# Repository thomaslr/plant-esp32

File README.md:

# 🌿 Plant Monitor & Automated Irrigation Controller (ESP32-C3 Rust)

An industrial-grade, memory-safe automated plant watering and environmental monitoring system built for the ultra-compact **ESP32-C3 SuperMini** (32-bit RISC-V) running on **ESP-IDF** and written in **bare-metal Rust**.

Features:
- **Zero Heap Fragmentation & Crash-Resilience:** Complete domain logic written in memory-safe Rust with 66+ unit tests passing on host (`cargo test`).
- **Dual-Slot A/B Over-The-Air (OTA) Updates:** Dual 1984 KB partitions (`ota_0` / `ota_1`) with hardware bootloader rollback (`CONFIG_BOOTLOADER_APP_ROLLBACK_ENABLE`). If a newly flashed firmware encounters an error, the chip automatically reverts to the previous working slot.
- **Embedded Web Dashboard & PWA:** Self-hosted interactive web dashboard embedded directly in flash via `include_str!`, installable as an offline-capable PWA on iOS, Android, and Desktop.
- **Fail-Safe Plant Protection:** Multi-tiered safety supervisor enforcing daily watering limits, minimum cycle cooldowns, dry tank cutoffs, and night-time quiet hours.
- **Self-Healing Wi-Fi Provisioning:** Captive portal (`PlantMonitor-Setup-XXXX`) with a 5-minute watchdog recovery timer that auto-reconnects when home routers recover after outages.
- **Deterministic Multi-Fault LED Supervisor:** Non-blocking blue LED telemetry signaling Wi-Fi status, pump state, active faults, and flash writing strobes.

---

## 🚀 Quick Start & Installation

Ready to get started? Check out our dedicated step-by-step guide:

👉 **[Complete Quick Start & Flashing Guide (QUICKSTART.md)](QUICKSTART.md)**

### At a Glance: Zero-Install Pre-Built Binaries

Every GitHub release includes two binary formats on the **[Releases Page](https://github.com/thomaslr/plant-esp32/releases)**:

| Binary File | Flash Address | Purpose & Usage |
| :--- | :---: | :--- |
| **`plant-firmware-factory.bin`** | **`0x0`** | **Initial Setup / First-Time Flashing:** Merged factory binary with ESP32-C3 bootloader, Dual-OTA partition table (`ota_0` and `ota_1`), and application code. Flashes blank chips in one shot via Chrome/Edge Web Flasher or USB CLI. |
| **`plant-firmware.bin`** | OTA Partition | **Wi-Fi Updates (OTA):** Standalone application payload uploaded via the web interface (`http://plants1.local`) or downloaded automatically during remote updates. |

* **1-Click Browser Flashing:** Open [Espressif Web Flasher](https://espressif.github.io/esptool-js/) in Chrome/Edge, connect your ESP32-C3 SuperMini at `460800` baud, and flash `plant-firmware-factory.bin` at `0x0`.
* **Single-Command CLI:** `esptool.py --chip esp32c3 write_flash 0x0 plant-firmware-factory.bin`
* **First-Time Wi-Fi Setup:** Connect to the `PlantMonitor-Setup-XXXX` hotspot at `http://192.168.4.1` to configure your Wi-Fi credentials.

See **[QUICKSTART.md](QUICKSTART.md)** for complete hardware checklists, bootloader button timings, and troubleshooting.

---

## 📌 Hardware Pinout Reference (ESP32-C3 SuperMini)

Canonical Pinout Reference: [LastMinuteEngineers ESP32-C3 SuperMini Pinout](https://lastminuteengineers.com/esp32-c3-super-mini-pinout-reference/)

| ESP32-C3 Pin | Connected Component | Function & Conditioning | Mode |
| :--- | :--- | :--- | :--- |
| **GPIO 0** | 18650 Battery Monitor | ADC1_CH0 via 100kΩ/100kΩ divider (R8/R9) + 100nF (C6) | Analog IN |
| **GPIO 1** | Ambient Light Sensor | ADC1_CH1 via LDR1 + 10kΩ divider (R7) + 100nF (C4) | Analog IN |
| **GPIO 2** | Strapping Protected | **Unconnected / High-Z** (Zero boot hangs) | High-Z |
| **GPIO 3** | Capacitive Soil Sensor | ADC1_CH3 connected to TB2 Pin 1 (`AOUT`) + 100nF filter (C2) | Analog IN |
| **GPIO 4** | 5V Supply Rail Monitor | ADC1_CH4 via 100kΩ/100kΩ divider (R1/R2) + 100nF filter (C1) | Analog IN |
| **GPIO 5** | I2C SCL | I2C Clock bus for optional SHT30 / BH1750 modules | Open Drain |
| **GPIO 6** | I2C SDA | I2C Data bus for optional SHT30 / BH1750 modules | Open Drain |
| **GPIO 7** | Ultrasonic Sensor `TRIG`| 10 µs trigger pulse output to HC-SR04 (TB1 Pin 2) | Digital OUT |
| **GPIO 8** | Onboard Status LED | Active LOW blue LED (Active: 0, Inactive: 1) | Digital OUT |
| **GPIO 9** | BOOT Button | Onboard tactile button (pulls LOW when pressed) | Digital IN |
| **GPIO 10** | Pump MOSFET Gate | Digital output to AO3400A Gate via 1kΩ (R5) + 100kΩ pull-down (R6) | Digital OUT |
| **GPIO 20** | Ultrasonic Sensor `ECHO`| Digital input via 1kΩ/2kΩ divider (R3/R4) stepping 5V down to 3.3V | Digital IN |
| **GPIO 21** | Switched Soil Sensor VCC | Digital switched 3.3V power to TB2 Pin 2 (Duty-cycled reading) | Digital OUT |

---

## 🛡️ Multi-Tiered Safety Supervisor

The watering pump can **never** physically run unless all safety invariants are satisfied simultaneously:
1. **Hardware Watchdog Timer (WDT):** 5-second hardware timeout resets the CPU if the scheduler stalls, pulling GPIO 10 LOW via R6 (100kΩ).
2. **Maximum Continuous Pump Runtime:** Hard cutoff after 60 seconds prevents tank emptying during pipe fractures.
3. **Minimum Cycle Cooldown:** Mandatory 300-second pause between watering events allows water absorption into soil substrate.
4. **Daily Cumulative Watering Limit:** Prevents root drowning by capping total daily watering duration (e.g. 93 seconds/day max), resetting at local midnight via SNTP.
5. **Night-Watering Protection:** Automated watering is inhibited during night quiet hours (default: 10:00 PM to 9:00 AM).
6. **Dry Tank Interlock:** Blocks automated and manual pump activation when reservoir water level is below 2.0 cm.

---

## 🔄 Dual-Slot Over-The-Air (OTA) Updates

The ESP32-C3 uses a custom 4MB partition table (`plant-firmware/partitions.csv`):
```text
nvs,      data, nvs,     0x9000,   0x6000,   # 24 KB User config & Wi-Fi credentials
otadata,  data, ota,     0xf000,   0x2000,   # 8 KB Active boot slot pointers (A/B state)
phy_init, data, phy,     0x11000,  0x1000,   # 4 KB RF calibration data
ota_0,    app,  ota_0,   0x20000,  0x1f0000, # 1984 KB Application Slot 0 (Active / Standby)
ota_1,    app,  ota_1,   0x210000, 0x1f0000, # 1984 KB Application Slot 1 (Active / Standby)
```

- When an update is initiated from the Web Dashboard or REST API, the firmware streams `plant-firmware.bin` from GitHub Releases into the inactive slot (`ota_0` or `ota_1`).
- On reboot, the bootloader attempts to boot the new slot. If it crashes or fails to call `mark_running_slot_valid()`, the bootloader automatically rolls back to the previous known-good firmware slot.

---

## 💡 Status LED Signal Reference

The onboard blue LED (GPIO 8) on the ESP32-C3 SuperMini provides real-time visual feedback:

| LED Pattern | Meaning & State |
| :--- | :--- |
| **💙 Single 100ms Pulse (every 10s)** | **Normal Healthy Idle:** All sensors within bounds, Wi-Fi connected. |
| **🌊 Solid ON** | **Watering Active:** Pump motor is running. |
| **⚡ 10 Hz Strobe (Continuous)** | **OTA Flashing:** Flash memory write in progress — do not unplug. |
| **📶 200ms ON / 800ms OFF** | **Wi-Fi Connecting / SoftAP:** In setup portal or negotiating router. |
| **🌐 Rapid Double Blip** | **Web Traffic:** Incoming HTTP REST API or dashboard request. |
| **⚠️ 3 Pulses + Pause** | **Soil Moisture Sensor Fault:** Disconnected or voltage out of bounds. |
| **⚠️ 4 Pulses + Pause** | **Ultrasonic Sensor Fault:** Echo timeout, echo blocked, or disconnected. |
| **📉 Accelerando Frequency Sweep** | **Reservoir Empty:** Water level below dry run safety threshold. |
| **🔘 Solid ON (held) + 5 Rapid Blips** | **Hardware Factory Reset:** Hold `BOOT` button (GPIO 9) for 5s until LED blinks 5 times to confirm wipe. |

---

## 🏠 Home Assistant Integration

Integrate the plant monitor into Home Assistant using standard REST sensors:

```yaml
# configuration.yaml
sensor:
  - platform: rest
    name: "Plant Monitor"
    resource: "http://plants1.local/api/telemetry"
    scan_interval: 30
    json_attributes:
      - soil_moisture_pct
      - water_level_pct
      - water_level_cm
      - light_level_pct
      - dli
      - battery_voltage_mv
      - is_watering
      - wifi_rssi
    value_template: "{{ 'online' if value_json.is_watering is defined else 'offline' }}"

  - platform: template
    sensors:
      plant_soil_moisture:
        friendly_name: "Soil Moisture"
        unit_of_measurement: "%"
        value_template: "{{ state_attr('sensor.plant_monitor', 'soil_moisture_pct') | round(1) }}"
        icon_template: mdi:flower
      plant_water_level:
        friendly_name: "Water Level"
        unit_of_measurement: "%"
        value_template: "{{ state_attr('sensor.plant_monitor', 'water_level_pct') | round(1) }}"
        icon_template: mdi:water-percent
      plant_light_dli:
        friendly_name: "Daily Light Integral (DLI)"
        unit_of_measurement: "mol/m²/d"
        value_template: "{{ state_attr('sensor.plant_monitor', 'dli') | round(2) }}"
        icon_template: mdi:white-balance-sunny

# Manual Watering Trigger Action
rest_command:
  water_plant:
    url: "http://plants1.local/api/water"
    method: POST
    content_type: "application/json"
    payload: '{"duration_sec": 5}'
```

---

## 📂 Repository Structure

```
plant-esp32/
├── .github/workflows/          # CI/CD: Automated builds and release publishing
│   └── build-and-release.yml   # Multi-binary builder (factory + OTA .bin)
├── data/                       # Embedded Web Frontend (HTML, CSS, JS, PWA manifest)
├── installer/                  # ESP Web Tools 1-click in-browser web installer
├── firmware-rust/              # Rust Cargo Workspace
│   ├── Cargo.toml
│   ├── plant-core/             # Platform-independent domain logic, safety supervisor, math
│   └── plant-firmware/         # ESP-IDF firmware application, HAL, HTTP server, OTA client
├── pcb/                        # KiCad PCB project, schematics, and manufacturing Gerbers
├── enclosure/                  # 3D printable CAD models and enclosures
├── scripts/                    # Developer helper scripts (flashing, pin tests)
├── QUICKSTART.md               # First-time setup, flashing & provisioning guide
├── PROJECT.md                  # Comprehensive architectural system specification
└── CHANGELOG.md                # Firmware changelog history
```

---

## 📄 License

This project is open source and dual-licensed across software and hardware (see [LICENSE](LICENSE) for full details):

| Component | Directories | License |
| :--- | :--- | :--- |
| **Software & Web UI** | [`firmware-rust/`](firmware-rust/), [`data/`](data/), [`installer/`](installer/), [`scripts/`](scripts/) | **[GNU GPLv3](LICENSE-SOFTWARE)** (`GPL-3.0-only`) |
| **Hardware & Enclosure** | [`pcb/`](pcb/), [`enclosure/`](enclosure/) | **[CERN-OHL-S v2](LICENSE-HARDWARE)** (`CERN-OHL-S-2.0`) |

### Commercial Licensing Available

Tinkerers, makers, and researchers are free to build, modify, and share this project under **GPLv3** and **CERN-OHL-S v2** (preserving attribution and publishing any distributed modifications under the same license).

Companies or organizations wishing to use, modify, or manufacture this project in a **closed-source or proprietary commercial product** without reciprocal source-disclosure obligations—or seeking official brand/trademark licensing—can obtain a commercial license. See [LICENSE](LICENSE) for contact details.

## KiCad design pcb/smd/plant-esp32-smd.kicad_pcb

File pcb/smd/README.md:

# Plant ESP32 Controller — Turnkey SMD / PCBA Edition (Rev 2.3)

This directory contains the production files, Pick & Place centroid files, Bill of Materials, and KiCad designs for the **Turnkey Surface Mount (SMD) Edition** of the Plant ESP32 watering controller.

Optimized specifically for **JLCPCB SMT Assembly** using **100% Basic Parts Library components** for zero feeder change fees ($0 setup fees).

---

## 3D Previews & Interactive Diagram

| Top View (SMD Components & Silkscreen) | Isometric 3D View (SMD) |
| :---: | :---: |
|  |  |

| Bottom View (Solid Ground Plane Pour & Power Routing) |
| :---: |
|  |

👉 **Interactive SVG Circuit Diagram & Net Visualizer:** [`circuit_diagram_smd.html`](circuit_diagram_smd.html)

---

## Architectural Highlights (Rev 2.3)

* **100% Top-Side SMT Placement**: All SMD parts are on the `F.Cu` / `F.Paste` layer, requiring only single-sided stencil setup ($0 double-sided setup fees).
* **100% Basic Parts Library ($0 Feeder Fees)**: All 8 unique SMD parts (R1–R9, C1–C6, D1, D2, Q1) are selected from JLCPCB's permanent Basic Parts catalog. Total feeder setup fee: **\$0.00**.
* **Authoritative Pinout Reference**: All pins match the official [LastMinuteEngineers ESP32-C3 SuperMini Pinout Reference](https://lastminuteengineers.com/esp32-c3-super-mini-pinout-reference/).
* **Dedicated Dual ADC Voltage Monitoring (Zero Jumpers!)**:
  * **No selector header or jumper shunt required (`JP1` eliminated completely)**. Both voltages are sampled concurrently in real time by firmware!
  * **5V Supply Rail Monitor (GPIO 4 / `ADC1_CH4`)**: Dedicated 100 kΩ / 100 kΩ divider (`R1`, `R2`, `#C149504`) + 100 nF filter (`C1`, `#C28233`). Monitors USB/Mains 5V health and detects pump brownouts.
  * **18650 Battery Monitor (GPIO 0 / `ADC1_CH0`)**: Dedicated 100 kΩ / 100 kΩ divider (`R8`, `R9`, `#C149504`) + 100 nF filter (`C6`, `#C28233`). Directly measures raw 18650 Li-ion battery voltage ($3.0\text{V}\text{–}4.2\text{V}$) from `TB4 Pin 3 (BAT)`. Quiescent drain is **only 21 µA** ($\sim 15\text{ mAh}$ per month), far below the battery's chemical self-discharge!
  * Both channels reside on **ADC1**, guaranteeing 100% reliable concurrent analog reads during active Wi-Fi streaming.
* **External Solar / 18650 Battery Power Terminal (`TB4`, DNP)**:
  * 3-pin KF301 screw terminal block (5.00 mm pitch) located on the right edge with wire entries facing outwards (`+X`).
  * **Pin 1 (`EXT_5V`)**: Regulated 5.0V power input from a solar charge & boost module (e.g. DD05CVSA mini-UPS).
  * **Pin 2 (`GND`)**: Common system ground.
  * **Pin 3 (`BAT`)**: Direct connection to the 18650 Li-ion battery positive terminal (`BAT+`) for true state-of-charge monitoring.
* **Anti-Backfeeding Schottky Diode Protection (`D2`)**:
  * **SS34** (SMA / DO-214AC package, 40V 3A Schottky rectifier, JLCPCB Basic Part `#C8678`, \$0 fee).
  * Placed in series between `TB4-1` (`EXT_5V`) and the internal `+5V` power rail.
  * When USB-C is plugged into the ESP32 while the battery/solar module is connected, `D2` is reverse-biased and **physically blocks 100% of reverse current** from backfeeding into the booster or solar charger.
  * Ultra-low forward drop ($\sim 0.25\text{–}0.35\text{V}$) delivers $\sim 4.75\text{V}$ to the board under pump load, well above the 3.5V ESP32 LDO brownout limit.
* **Flyback Diode (`D1`)**: **SS34** (SMA / DO-214AC package, 40V 3A Schottky rectifier, JLCPCB Basic Part `#C8678`, shared reel with D2).
* **Logic-Level High-Current MOSFET (`Q1`)**: **AO3400A** (SOT-23-3, 30V 5.7A, $V_{GS(th)} \approx 0.65\text{–}1.45\text{V}$, $R_{DS(on)} < 0.033\,\Omega$, LCSC `#C20917`). Gate driven by **GPIO 10**.
* **Dual-Stage Brownout & High-Frequency Decoupling**:
  * **Factory Pre-Soldered Ceramics (`C3`, `C5`)**: 2× 10 µF 25V 0805 MLCCs (LCSC `#C15850`, Basic Part, $0 fee). Total 20 µF with ultra-low ESR ($< 0.02\,\Omega$) handles microsecond motor startup dips and Wi-Fi bursts.
  * **Through-Hole Brownout Expansion (`C_EXT`, DNP)**: 2.50 mm pitch radial footprint (labeled `OPT BULK` on silkscreen, supporting Ø6.3 mm to Ø10.0 mm cans) located on the far right directly adjacent to pump terminal TB3 (>55 mm away from the ESP32 USB-C port). Leaves the entire USB-C corridor 100% unobstructed.
* **Switched Soil Sensor Power on GPIO 21 & Analog DATA on GPIO 3**:
  * Duty-cycled soil power is assigned to `GPIO 21` (digital out on header J2-8, routed to `TB2-2`).
  * Capacitive probe analog output is sampled on `GPIO 3` (`ADC1_CH3` on header J1-5, routed from `TB2-1`).
* **Ambient Light Sensor LDR Divider on GPIO 1 (`ADC1_CH1`)**:
  * **Zero Boot Strapping Risk**: Placed on **GPIO 1** (`ADC1_CH1`) to completely eliminate boot hangs.
  * **LDR1 (DNP)**: 2-pin through-hole footprint (2.54 mm pitch) for **GL5506, GL5516, GL5528, GL5537, GL5539** photoresistors.
  * **R7 (10 kΩ 0805 SMD)**: Factory pre-soldered basic part ($V_{out} \to$ GPIO 1).
  * **C4 (100 nF 0805 SMD)**: Factory pre-soldered basic part for AC light flicker suppression.
  * **100% Wi-Fi Safe**: Because GPIO 1 is on **ADC1**, `analogRead(1)` functions seamlessly while Wi-Fi is actively streaming.
* **Ultrasonic Sensor on GPIO 7 (TRIG) & GPIO 20 (ECHO)**:
  * Ultrasonic TRIG is assigned to **GPIO 7** (digital out on header J2-3, routed to `TB1-2`).
  * Ultrasonic ECHO is assigned to **GPIO 20** via the 1k/2k 0805 level divider (`TB1-3` $\to$ R3/R4 $\to$ J2-7).
* **GPIO 2 Left Unconnected**: Protected strapping pin left free on header J1-6 to ensure rock-solid boot reliability under all conditions.
* **I2C Expansion Ports for SHT30 & BH1750 (DNP)**:
  * **MOD1 (SHT30 Socket)**: 4-pin header (`3V3`, `GND`, `SCL` $\to$ GPIO 5, `SDA` $\to$ GPIO 6).
  * **MOD2 (BH1750 Socket)**: 5-pin header (`VCC`, `GND`, `SCL` $\to$ GPIO 5, `SDA` $\to$ GPIO 6, `ADD` $\to$ GND for default `0x23` address).
  * Both headers are left unpopulated (DNP) by JLCPCB at **\$0.00 extra cost**, giving an instant drop-in upgrade path.

---

## Bill of Materials (BOM) & LCSC Part Mapping

| Designator | Value / Description | Package | JLCPCB Part # (LCSC) | Type | Role |
| :--- | :--- | :--- | :--- | :--- | :--- |
| **R1, R2, R6, R8, R9** | 100 kΩ (1%, 1/8W) | 0805 SMD | **C149504** | Basic (\$0 Fee) | 5V Divider / Battery Divider (21µA drain) / Gate Pull-Down |
| **R7** | 10 kΩ (1%, 1/8W) | 0805 SMD | **C17414** | Basic (\$0 Fee) | LDR Ambient Light Sensor Divider |
| **R3, R5** | 1 kΩ (1%, 1/8W) | 0805 SMD | **C17513** | Basic (\$0 Fee) | Echo Divider High-Side / Gate Current Limiter |
| **R4** | 2 kΩ (1%, 1/8W) | 0805 SMD | **C17604** | Basic (\$0 Fee) | Echo Divider Low-Side ($5\text{V} \to 3.3\text{V}$) |
| **C1, C2, C4, C6** | 100 nF (50V X7R) | 0805 SMD | **C28233** | Basic (\$0 Fee) | 5V ADC Filter / Soil RF Bypass / Light Filter / Battery ADC Filter |
| **C3, C5** | 10 µF (25V X5R) | 0805 SMD | **C15850** | Basic (\$0 Fee) | 5V Power Rail Transient Decoupling (20 µF Total) |
| **D1, D2** | SS34 (3A, 40V Schottky Barrier Diode) | SMA (DO-214AC) | **C8678** | Basic (\$0 Fee) | Flyback Clamping (D1) & Anti-Backfeed Diode (D2) |
| **Q1** | AO3400A (30V, 5.7A N-Channel MOSFET) | SOT-23-3 | **C20917** | Basic (\$0 Fee) | Submersible Pump Low-Side Switch |

*Hand-soldered after delivery (or left unpopulated):*
* **J1, J2**: 2× 1×8 Female Pin Header (2.54 mm pitch, through-hole)
* **TB1 (TB1 - Ultra)**: KF301-4P (5.00 mm pitch 4-pin screw terminal, Ultrasonic)
* **TB2 (TB2 - Soil)**: KF301-3P (5.00 mm pitch 3-pin screw terminal, Soil Moisture)
* **TB3 (TB3 - Motor)**: KF301-2P (5.00 mm pitch 2-pin screw terminal, 5V Water Pump)
* **TB4 (EXT PWR)**: KF301-3P (5.00 mm pitch 3-pin screw terminal, External Solar / 18650 Battery Power)
* **LDR1**: GL55xx Photoresistor (2-pin 2.54 mm through-hole, DNP)
* **MOD1**: SHT30 Temperature & Humidity Module (4-pin 2.54 mm socket, DNP)
* **MOD2**: BH1750 Ambient Light Module (5-pin 2.54 mm socket, DNP)
* **C_EXT**: 100 µF – 470 µF Radial Electrolytic (2.50 mm pitch, D6.3 mm – D8.0 mm, DNP optional brownout buffer)

---

## Production Files

* 📦 **Gerber & Drill Package**: [`plant-esp32-smd_gerbers.zip`](plant-esp32-smd_gerbers.zip)
* 📋 **SMT Assembly BOM (JLCPCB)**: [`plant-esp32-smd_bom.csv`](plant-esp32-smd_bom.csv) (SMT parts only, 100% CPL match)
* 📋 **Hand-Solder BOM**: [`plant-esp32-smd_hand_solder_bom.csv`](plant-esp32-smd_hand_solder_bom.csv) (Through-hole connectors)
* 📍 **Pick & Place Centroid File**: [`plant-esp32-smd_cpl.csv`](plant-esp32-smd_cpl.csv)
* 📐 **KiCad PCB File**: [`plant-esp32-smd.kicad_pcb`](plant-esp32-smd.kicad_pcb)
* 📄 **KiCad Schematic**: [`plant-esp32-smd.kicad_sch`](plant-esp32-smd.kicad_sch)
* 🌐 **Interactive Circuit Diagram**: [`circuit_diagram_smd.html`](circuit_diagram_smd.html)
* 🛡️ **DRC Verification Report**: [`drc_report_smd.txt`](drc_report_smd.txt) (**0 Errors, 0 Warnings, 0 Unconnected Nets**)
* 🐍 **Generator Script**: [`generate_pcb_smd.py`](generate_pcb_smd.py)

---

## Ordering on JLCPCB

1. Go to **[jlcpcb.com](https://jlcpcb.com/)** and click **"Add Gerber file"**.
2. Upload `plant-esp32-smd_gerbers.zip`. The dimensions ($74 \times 54\,\text{mm}$) and 2 layers are automatically detected.
3. Under **PCB Assembly**, toggle **"PCB Assembly"** to **ON**:
   * **Assembly Side**: Top Side
   * **PCBA Qty**: 5 (or 2)
   * **Tooling Holes**: Added by JLCPCB
4. Proceed to the SMT component upload page:
   * **BOM File**: Upload `plant-esp32-smd_bom.csv`
   * **CPL / Centroid File**: Upload `plant-esp32-smd_cpl.csv`
5. Review matched components:
   * All 9 unique SMD parts match directly to their pre-assigned LCSC part numbers.
   * Feeder setup fees show as **\$0.00**.
6. Review the Component Placement preview screen and confirm alignments.
7. Checkout. When boards arrive, hand-solder the screw terminals and headers as needed.

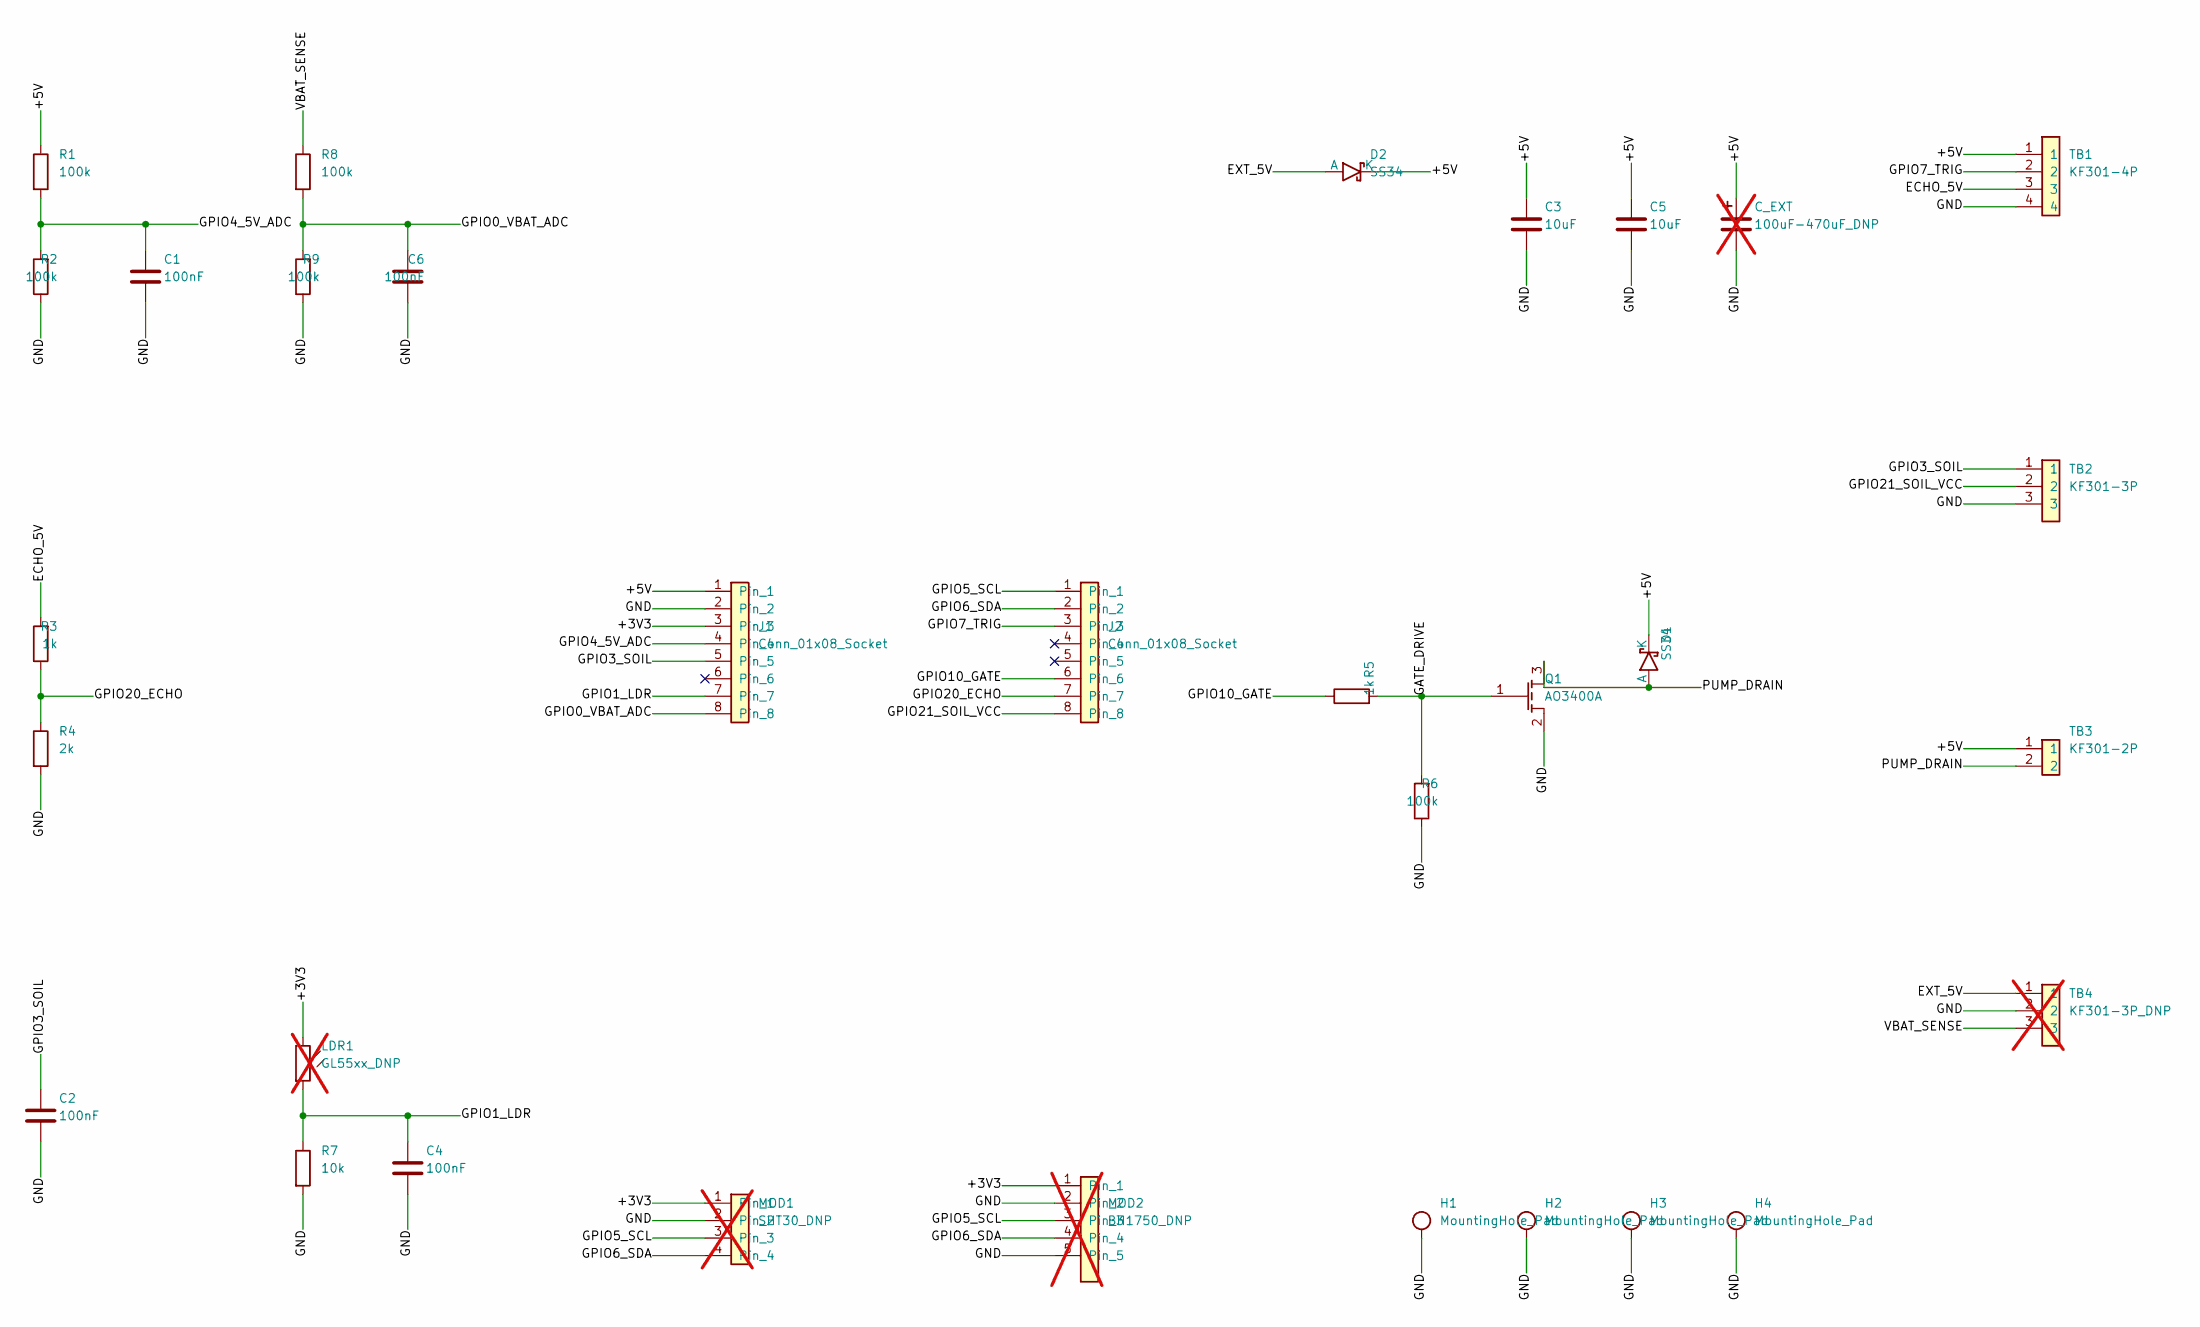
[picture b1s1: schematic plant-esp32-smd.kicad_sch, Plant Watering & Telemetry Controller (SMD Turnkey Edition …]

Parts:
C1, C2, C4, C6: 100nF; C_0805_2012Metric; LCSC C28233
C3, C5: 10uF; C_0805_2012Metric; LCSC C15850
C_EXT: 100uF-470uF_DNP; CP_Radial_D6.3mm_P2.50mm; not fitted
D1, D2: SS34; D_SMA; LCSC C8678
H1, H2, H3, H4: MountingHole_Pad; MountingHole_3.2mm_M3_Pad
J1, J2: Conn_01x08_Socket; PinSocket_1x08_P2.54mm_Vertical; LCSC C224346
LDR1: GL55xx_DNP; PinHeader_1x02_P2.54mm_Vertical; not fitted
MOD1: SHT30_DNP; PinSocket_1x04_P2.54mm_Vertical; not fitted
MOD2: BH1750_DNP; PinSocket_1x05_P2.54mm_Vertical; not fitted
Q1: AO3400A; SOT-23; LCSC C20917
R1, R2, R6, R8, R9: 100k; R_0805_2012Metric; LCSC C149504
R3, R5: 1k; R_0805_2012Metric; LCSC C17513
R4: 2k; R_0805_2012Metric; LCSC C17604
R7: 10k; R_0805_2012Metric; LCSC C17414
TB1: KF301-4P; TerminalBlock_KF301-4P_P5.00mm; LCSC C8354
TB2: KF301-3P; TerminalBlock_KF301-3P_P5.00mm; LCSC C8353
TB3: KF301-2P; TerminalBlock_KF301-2P_P5.00mm; LCSC C8352
TB4: KF301-3P_DNP; TerminalBlock_KF301-3P_P5.00mm_Vertical; LCSC C8353; not fitted

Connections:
+3V3: J1.3, LDR1.1, MOD1.1, MOD2.1
+5V: C3.1, C5.1, C_EXT.1, D1.1 (K), D2.1 (K), J1.1, R1.1, TB1.1, TB3.1
ECHO_5V: R3.2, TB1.3
EXT_5V: D2.2 (A), TB4.1
GATE_DRIVE: Q1.1 (G), R5.2, R6.2
GND: C1.2, C2.2, C3.2, C4.2, C5.2, C6.1, C_EXT.2, H1.1, H2.1, H3.1, H4.1, J1.2, MOD1.2, MOD2.2, MOD2.5, Q1.2 (S), R2.1, R4.2, R6.1, R7.2, R9.1, TB1.4, TB2.3, TB4.2
GPIO0_VBAT_ADC: C6.2, J1.8, R8.2, R9.2
GPIO1_LDR: C4.1, J1.7, LDR1.2, R7.1
GPIO3_SOIL: C2.1, J1.5, TB2.1
GPIO4_5V_ADC: C1.1, J1.4, R1.2, R2.2
GPIO5_SCL: J2.1, MOD1.3, MOD2.3
GPIO6_SDA: J2.2, MOD1.4, MOD2.4
GPIO7_TRIG: J2.3, TB1.2
GPIO10_GATE: J2.6, R5.1
GPIO20_ECHO: J2.7, R3.1, R4.1
GPIO21_SOIL_VCC: J2.8, TB2.2
PUMP_DRAIN: D1.2 (A), Q1.3 (D), TB3.2
VBAT_SENSE: R8.1, TB4.3

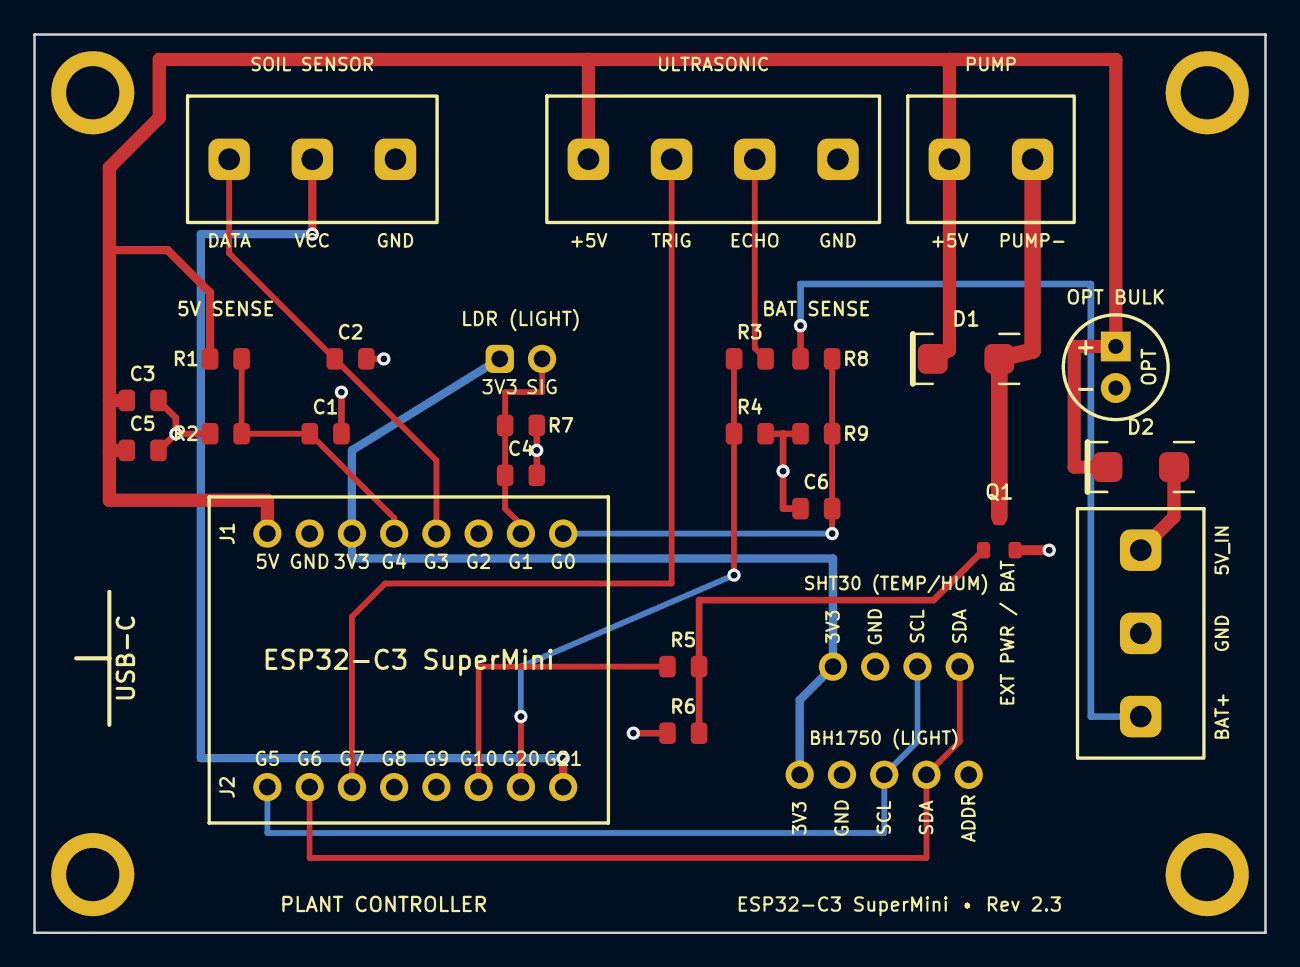
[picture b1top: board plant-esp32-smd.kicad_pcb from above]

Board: 2 copper layers, 74.0 x 54.0 mm, 32 parts (0 on the bottom side), 18 nets.

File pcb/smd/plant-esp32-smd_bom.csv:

Comment,Designator,Footprint,LCSC Part Number,Type
100k,R1 R2 R6 R8 R9,0805,C149504,Basic
10k,R7,0805,C17414,Basic
1k,R3 R5,0805,C17513,Basic
2k,R4,0805,C17604,Basic
100nF,C1 C2 C4 C6,0805,C28233,Basic
10uF,C3 C5,0805,C15850,Basic
SS34,D1 D2,SMA,C8678,Basic
AO3400A,Q1,SOT-23,C20917,Basic

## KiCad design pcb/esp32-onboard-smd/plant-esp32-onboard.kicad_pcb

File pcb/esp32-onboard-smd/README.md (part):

# Plant ESP32 Controller — Monolithic Onboard SMD Edition (Rev 1.0)

This directory contains the production files, Pick & Place centroid files (CPL), Bill of Materials (BOM), KiCad design source files, and 3D renders for the **Monolithic Onboard SMD Edition** of the Plant ESP32 watering controller.

Rather than mounting an ESP32-C3 SuperMini daughterboard via pin headers, this turnkey edition integrates the official **Espressif ESP32-C3-WROOM-02** Wi-Fi + BLE 5 module directly onto the PCB, complete with native USB-C, onboard AMS1117-3.3 power regulation, tactile RESET & BOOT buttons, status/power LEDs, and multi-stage filtering.

Optimized specifically for **JLCPCB SMT Assembly** using **100% Top-Side placement** and prioritizing JLCPCB Basic Parts to keep assembly setup fees to an absolute minimum ($9.00 total for only 3 extended part reels across the entire production run).

---

## 3D Previews & Interactive Diagram

| Top View (Integrated ESP32-C3 & SMT Components) | Isometric 3D View |
| :---: | :---: |
|  |  |

| Bottom View (Ground Plane & Solder Mask) |
| :---: |
|  |

👉 **Interactive SVG Circuit Diagram & Net Visualizer:** [`circuit_diagram_onboard.html`](circuit_diagram_onboard.html)

---

## Architectural Highlights (Rev 1.0)

* **Monolithic Single-Board Design**:
  * Eliminates daughterboard pin headers, loose sockets, and manual solder alignment issues.
  * Direct solder attachment of the official **ESP32-C3-WROOM-02** module with 18 perimeter castellations and a large central thermal ground slug.
* **100% Top-Side SMT Assembly**:
  * All surface-mount components reside exclusively on the top (`F.Cu` / `F.Paste`) layer.
  * Requires only a single-sided SMT stencil, eliminating double-sided stencil and assembly setup fees.
* **Aggressive Feeder Cost Minimization ($9.00 Total Loading Fee)**:
  * **Basic Parts ($0 loading fee)**: All 0805 passives (resistors, MLCC capacitors), AMS1117-3.3 LDO (SOT-223), AO3400A MOSFET (SOT-23), SS34 Schottky diodes (SMA), and 0805 LEDs are sourced from JLCPCB's permanent Basic Parts library.
  * **Extended Parts (Only 3 reels)**:
    1. ESP32-C3-WROOM-02 (`C2934487`) — $3.00 feeder fee
    2. USB-C 16-Pin Receptacle `TYPE-C-31-M-12` (`C165948`) — $3.00 feeder fee
    3. TS-1187A SMD Tactile Pushbutton (`C318884`, shared by SW1 & SW2) — $3.00 feeder fee
* **Native USB-C CDC/JTAG Connectivity**:
  * Reversible 16-pin USB Type-C receptacle with dual 5.1 kΩ pulldown resistors (`R12`, `R13`) on CC1/CC2 for full USB-PD and C-to-C cable compliance.
  * Differential data pair (`D+` / `D-`) routes directly to the ESP32-C3 hardware USB CDC/JTAG peripheral (`GPIO 19` and `GPIO 18`), enabling direct flashing, bootloader entry, and serial monitoring without external USB-to-UART bridge ICs (no CP2102 or CH340 needed).
* **Dedicated Dual ADC Voltage Monitoring (Zero Jumpers)**:
  * **5V Supply Rail Monitor (GPIO 0 / `ADC1_CH0`)**: Dedicated 100 kΩ / 100 kΩ divider (`R1`, `R2`) + 100 nF filter (`C1`). Continuously verifies USB/Mains 5V health and detects pump brownouts.
  * **18650 Battery Monitor (GPIO 4 / `ADC1_CH4`)**: Dedicated 100 kΩ / 100 kΩ divider (`R8`, `R9`) + 100 nF filter (`C6`). Directly measures raw 18650 Li-ion battery voltage ($3.0\text{V}\text{–}4.2\text{V}$) from `TB4 Pin 3 (BAT)`. Quiescent drain is **only 21 µA** ($\sim 15\text{ mAh}$ per month), far below the battery's chemical self-discharge!
  * Both channels reside on **ADC1**, guaranteeing 100% reliable concurrent analog reads during active Wi-Fi streaming.
* **Dual Power Input Architecture with Anti-Backfeed Protection**:
  * **USB-C 5V Input**: Powers the board and pump during development, desktop testing, or permanent indoor mains operation.
  * **External Solar / Battery 5V Input (`TB4-1`)**: Connects to an external solar charge & boost module (e.g. DD05CVSA mini-UPS).
  * **Anti-Backfeeding Schottky Diode (`D2`)**: 40V 3A SS34 Schottky diode (`#C8678`) placed in series between `TB4-1` (`EXT_5V`) and the internal `+5V` rail. Blocks 100% of reverse current from backfeeding into the solar module when USB-C is plugged in.
* **Robust Power Regulation & Decoupling**:
  * **AMS1117-3.3 LDO (`U2`, SOT-223, Basic Part `#C475931`)**: Delivers up to 1000 mA of clean 3.3V logic power with wide copper tab heatsinking.
  * Multi-stage ceramic filtering: 10 µF (`C10`) + 100 nF (`C7`) at LDO input; 10 µF (`C11`) + 100 nF (`C8`) + 22 µF (`C12`) at LDO output directly adjacent to the ESP32 3V3 power pin.
* **Hardware Pushbuttons & Status Indicators**:
  * **RESET Button (`SW1`)**: Pulls `EN` to GND. Debounced by a 10 kΩ pull-up (`R10`) and 1 µF capacitor (`C9`).
  * **BOOT Button (`SW2`)**: Pulls `GPIO 9` to GND for manual ROM bootloader entry. Pulled high by 10 kΩ (`R11`).
  * **PWR LED (`D3`, Green)**: Indicates 3.3V rail health.
  * **STAT LED (`D4`, Blue)**: Active-low status indicator driven by `GPIO 8` via 1 kΩ resistor (`R15`). Connected to +3.3V to ensure GPIO 8 is pulled HIGH during boot strapping.
* **RF Optimization & Antenna Keepout**:
  * ESP32-C3-WROOM-02 inverted-F antenna points outward toward the bottom board edge.
  * Full copper keepout (no ground plane, no traces, no vias on top or bottom copper) under the antenna keepout zone.

---

## Bill of Materials (BOM) & LCSC Part Mapping

### SMT Assembly Parts (Factory Pre-Soldered by JLCPCB)

| Designator | Value / Description | Package | JLCPCB Part # (LCSC) | Type | Role |
| :--- | :--- | :--- | :--- | :--- | :--- |
| **U1** | ESP32-C3-WROOM-02-N4 (4MB Flash) | Module (18×25.5mm) | **C2934560** | Extended ($3) | Main RISC-V SoC (Wi-Fi + BLE 5, PCB Antenna) |
| **U2** | AMS1117-3.3 (3.3V 1A LDO) | SOT-223 | **C6186** | Basic ($0) | 5V to 3.3V Voltage Regulator |
| **J1** | TYPE-C-31-M-12 (16-Pin USB-C) | SMT Receptacle | **C165948** | Extended ($3) | Power & Native USB CDC/JTAG Data |
| **SW1, SW2** | TS-1187A-B-A-B Tactile Pushbutton | SMT Button | **C318884** | Extended ($3) | Hardware RESET and BOOT Switches |
| **Q1** | AO3400A (30V 5.7A N-Ch MOSFET) | SOT-23-3 | **C20917** | Basic ($0) | Submersible Water Pump Low-Side Switch |
| **D1, D2** | SS34 (3A 40V Schottky Diode) | SMA (DO-214AC) | **C8678** | Basic ($0) | Flyback Diode (D1) & Anti-Backfeed Diode (D2) |
| **D3** | Green LED (KT-0805G) | 0805 | **C2297** | Basic ($0) | 3.3V Power Good Indicator |
| **D4** | Blue LED (KT-0805B) | 0805 | **C2293** | Extended ($3) | Status Indicator (Active-Low on GPIO 8) |
| **R1, R2, R6, R8, R9** | 100 kΩ (1%, 1/8W) | 0805 SMD | **C149504** | Basic ($0) | 5V Divider / Battery Divider / Gate Pulldown |
| **R7, R10, R11** | 10 kΩ (1%, 1/8W) | 0805 SMD | **C17414** | Basic ($0) | LDR Divider / EN Pullup / BOOT Pullup |
| **R12, R13** | 5.1 kΩ (1%, 1/8W) | 0805 SMD | **C27834** | Basic ($0) | USB-C Configuration Channel CC1/CC2 Pulldowns |
| **R3, R5, R14, R15** | 1 kΩ (1%, 1/8W) | 0805 SMD | **C17513** | Basic ($0) | Echo High-Side / Gate Resistor / LED Resistors |
| **R4** | 2 kΩ (1%, 1/8W) | 0805 SMD | **C17604** | Basic ($0) | Echo Low-Side Level Divider ($5\text{V} \to 3.3\text{V}$) |
| **C1, C2, C4, C6, C7, C8**| 100 nF (50V X7R) | 0805 SMD | **C28233** | Basic ($0) | ADC Filters / RF Bypasses / LDO Decoupling |
| **C9** | 1 µF (50V X7R) | 0805 SMD | **C28323** | Basic ($0) | EN / Hardware Reset Debounce Filter |
| **C10, C11** | 10 µF (25V X5R) | 0805 SMD | **C15850** | Basic ($0) | LDO Input and Output Bulk MLCC Capacitors |
| **C12** | 22 µF (10V X5R) | 0805 SMD | **C45783** | Basic ($0) | ESP32-C3 VDD Power Rail Transient Buffer |

### Through-Hole Connectors & Hand-Soldered Parts (or DNP)

| Designator | Value / Description | Package | JLCPCB Part # (LCSC) | Notes |
| :--- | :--- | :--- | :--- | :--- |
| **TB1** | KF301-4P (5.00mm Pitch 4-Pin) | Through-Hole Terminal | **C8913** | Ultrasonic Sensor (5V, TRIG, ECHO, GND) |
| **TB2** | KF301-3P (5.00mm Pitch 3-Pin) | Through-Hole Terminal | **C8912** | Soil Moisture Sensor (DATA, VCC, GND) |
| **TB3** | KF301-2P (5.00mm Pitch 2-Pin) | Through-Hole Terminal | **C8911** | 5V Water Pump Motor (+5V, DRAIN) |
| **TB4** | KF301-3P (5.00mm Pitch 3-Pin) | Through-Hole Terminal | **C8912** | External Power & Battery (EXT_5V, GND, BAT) |
| **MOD1** | 1×4 Female Pin Header (2.54mm) | Through-Hole Header | — | SHT30 Temp/Humidity Sensor Socket (DNP) |
| **MOD2** | 1×5 Female Pin Header (2.54mm) | Through-Hole Header | — | BH1750 Light Sensor Socket (DNP) |
| **LDR1** | GL55xx Photoresistor (2-Pin 2.54mm) | Radial Through-Hole | — | Ambient Light Sensor (DNP) |
| **C_EXT** | 100 µF – 470 µF Radial Electrolytic | Radial (Ø6.3–8.0mm, P2.5mm)| — | Optional Heavy Motor Brownout Buffer (DNP) |

---

## Production Files

* 📦 **Gerber & Drill Package**: [`plant-esp32-onboard_gerbers.zip`](plant-esp32-onboard_gerbers.zip) (Contains Protel RS-274X Gerbers and separate PTH/NPTH drill files)
* 📋 **SMT Assembly BOM (JLCPCB)**: [`plant-esp32-onboard_bom.csv`](plant-esp32-onboard_bom.csv) (100% CPL match with verified LCSC part numbers)
* 📍 **Pick & Place Centroid File**: [`plant-esp32-onboard_cpl.csv`](plant-esp32-onboard_cpl.csv) (Aux origin at bottom-left corner `(0.0, 54.0)`, all coordinates strictly positive)
* 📋 **Hand-Solder BOM**: [`plant-esp32-onboard_hand_solder_bom.csv`](plant-esp32-onboard_hand_solder_bom.csv)
* 📐 **KiCad PCB File**: [`plant-esp32-onboard.kicad_pcb`](plant-esp32-onboard.kicad_pcb)
* 📄 **KiCad Schematic**: [`plant-esp32-onboard.kicad_sch`](plant-esp32-onboard.kicad_sch)
* 🌐 **Interactive Circuit Diagram**: [`circuit_diagram_onboard.html`](circuit_diagram_onboard.html)
* 🛡️ **DRC Verification Report**: [`drc_report_onboard.txt`](drc_report_onboard.txt) (**0 Violations, 0 Unconnected Nets**)

---

## Cost Breakdown (Per 10 Boards)

| Item | Unit Cost | Total (10 Boards) | Notes |
| :--- | :--- | :--- | :--- |
| **PCB Fabrication (2-Layer FR4, 74×54mm)** | ~$0.40 | ~$4.00 | Standard green solder mask, HASL lead-free |
| **SMT Setup & Stencil Fee** | — | ~$7.00 | Single-sided top SMT assembly |
| **Extended Part Loading Fees (3 Reels)** | $3.00 / reel | $9.00 | ESP32-C3 ($3), USB-C ($3), Buttons ($3) |
| **Basic Part Loading Fees (Passives, LDO, AO3400A, SS34)** | $0.00 | $0.00 | **$0 loading fees** |
| **Component Costs (SMT Parts for 10 boards)** | ~$1.80 / board | ~$18.00 | ESP32-C3 ($1.40), USB-C ($0.12), LDO ($0.08), Passives ($0.20) |
| **Total Estimated SMT Production Cost** | **~$3.80 / board** | **~$38.00** | **Completely assembled turnkey boards!** |

---

## ESP32-C3-WROOM-02 GPIO Pinout Table

| GPIO Pin | Pin Name | Peripheral / Signal | Hardware Role & Circuit Connection |
| :--- | :--- | :--- | :--- |
| **GPIO 0** | `ADC1_CH0` | 5V Rail Sense | High-impedance 100k/100k voltage divider (`R1`, `R2`) + 100nF filter (`C1`) |
| **GPIO 1** | `ADC1_CH1` | Soil Moisture Data | Connects to `TB2 Pin 1` with 100nF RF noise bypass (`C2`) |
| **GPIO 3** | `ADC1_CH3` | Ambient Light Sense | Voltage divider with LDR1 photoresistor and 10k resistor (`R7`) + 100nF filter (`C4`) |
| **GPIO 4** | `ADC1_CH4` | 18650 Battery Sense | High-impedance 100k/100k voltage divider (`R8`, `R9`) from `TB4 Pin 3` (21 µA drain) |
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
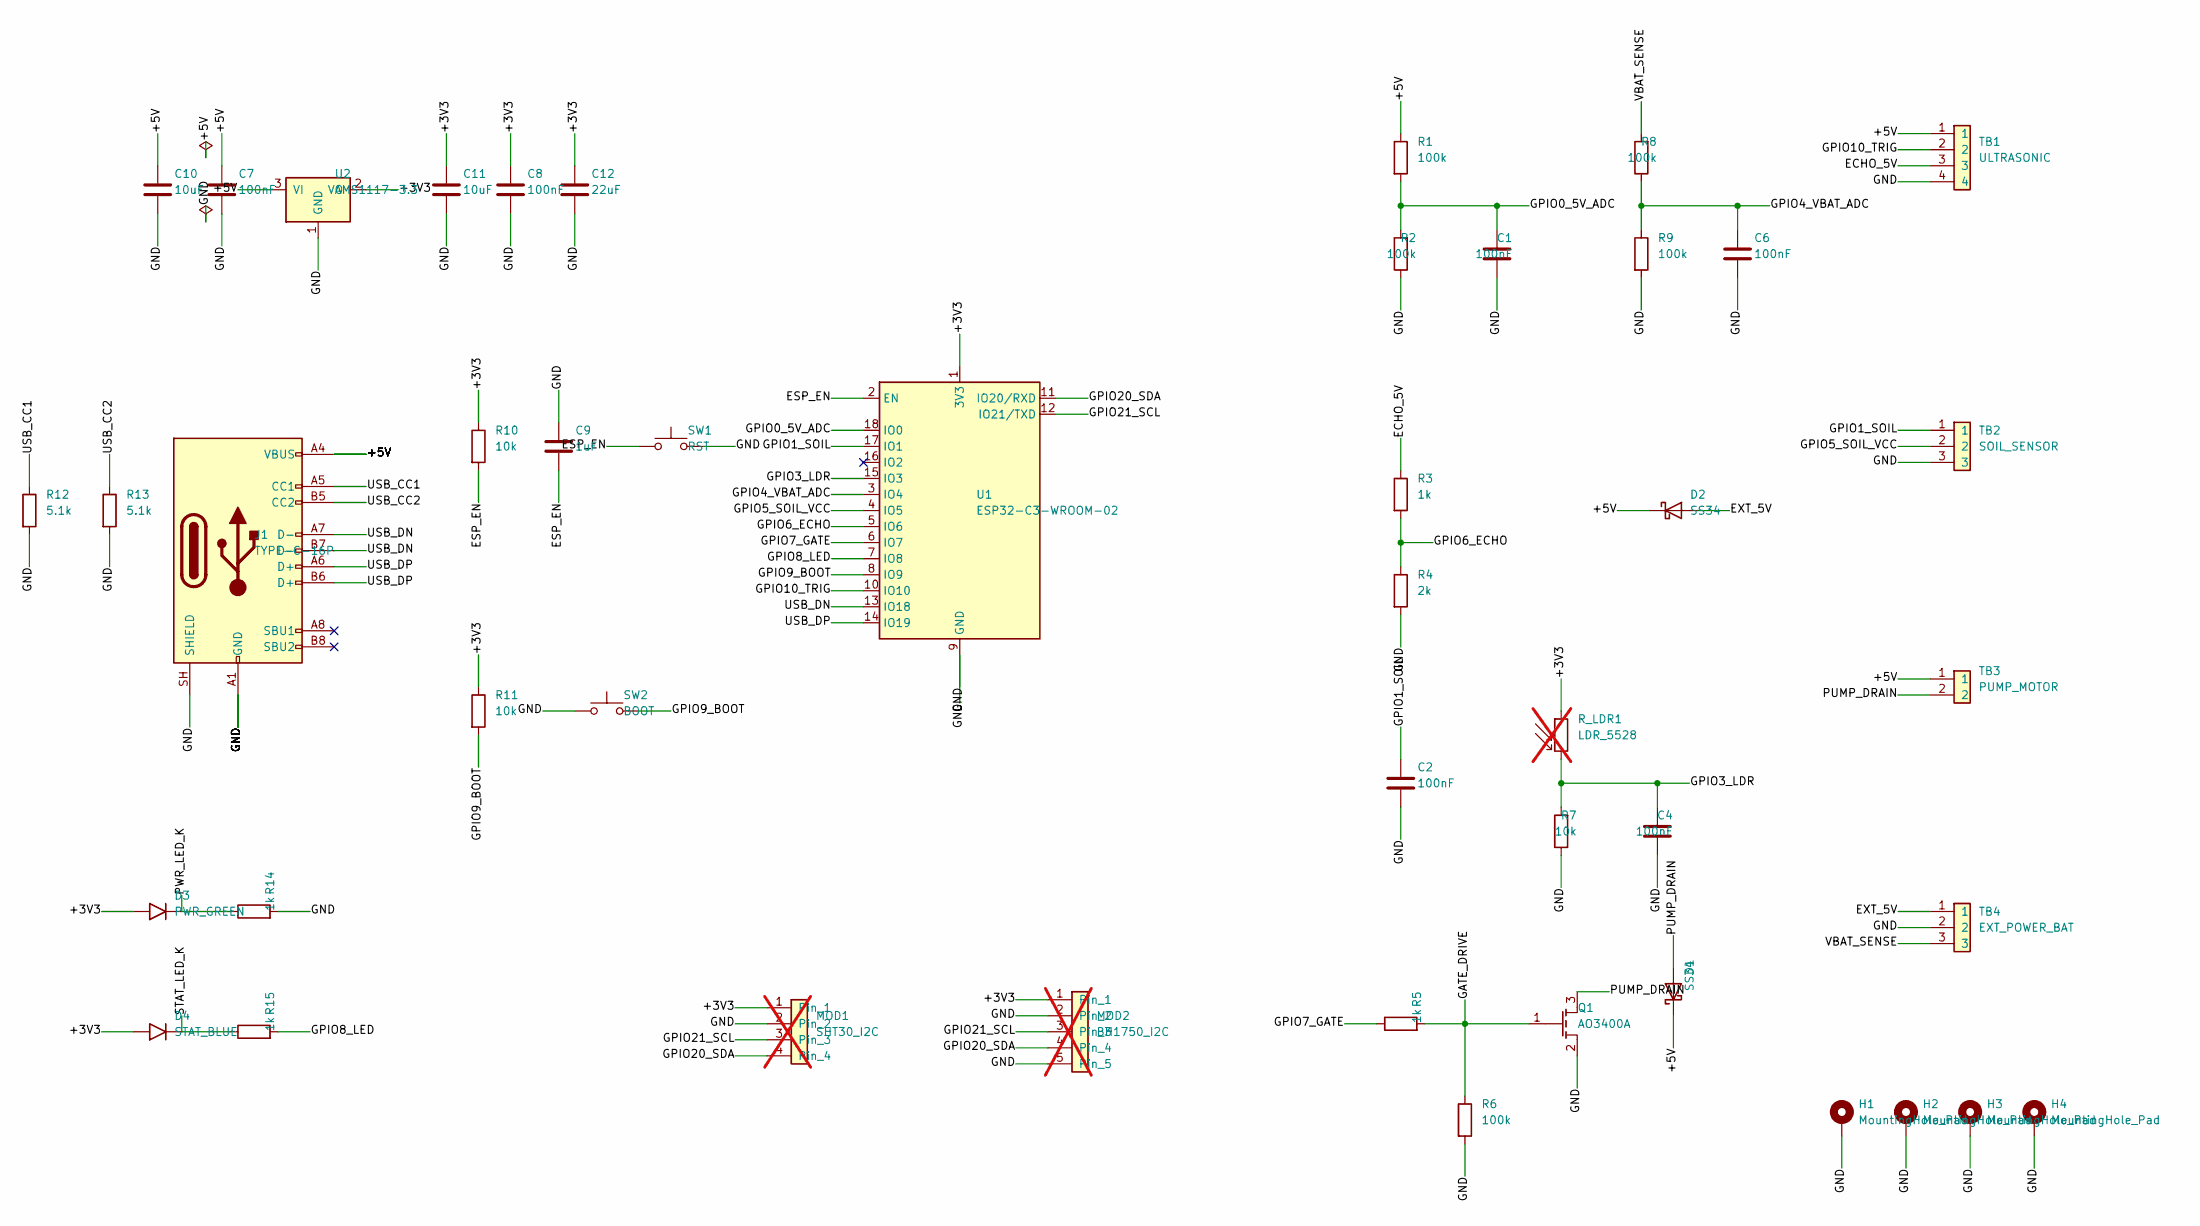
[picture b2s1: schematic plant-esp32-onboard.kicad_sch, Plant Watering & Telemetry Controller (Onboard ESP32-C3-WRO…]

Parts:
C1, C2, C4, C6, C7, C8: 100nF; C_0805_2012Metric; LCSC C28233
C9: 1uF; C_0805_2012Metric; LCSC C28323
C10, C11: 10uF; C_0805_2012Metric; LCSC C15850
C12: 22uF; C_0805_2012Metric; LCSC C45783
D1, D2: SS34; D_SMA; LCSC C8678
D3: PWR_GREEN; LED_0805_2012Metric; LCSC C2297
D4: STAT_BLUE; LED_0805_2012Metric; LCSC C2293
H1, H2, H3, H4: MountingHole_Pad; MountingHole_3.2mm_M3_Pad
J1: TYPE-C-16P; USB_C_Receptacle_HRO_TYPE-C-31-M-12; LCSC C165948
MOD1: SHT30_I2C; PinSocket_1x04_P2.54mm_Vertical; not fitted
MOD2: BH1750_I2C; PinSocket_1x05_P2.54mm_Vertical; not fitted
Q1: AO3400A; SOT-23; LCSC C20917
R1, R2, R6, R8, R9: 100k; R_0805_2012Metric; LCSC C149504
R3, R5, R14, R15: 1k; R_0805_2012Metric; LCSC C17513
R4: 2k; R_0805_2012Metric; LCSC C17604
R7, R10, R11: 10k; R_0805_2012Metric; LCSC C17414
R12, R13: 5.1k; R_0805_2012Metric; LCSC C27834
R_LDR1: LDR_5528; R_LDR_5.1x4.3mm_P3.4mm_Vertical; not fitted
SW1: RST; SW_Push_1P1T_XKB_TS-1187A; LCSC C318884
SW2: BOOT; SW_Push_1P1T_XKB_TS-1187A; LCSC C318884
TB1: ULTRASONIC; TerminalBlock_KF301-4P_P5.00mm; LCSC C8354
TB2: SOIL_SENSOR; TerminalBlock_KF301-3P_P5.00mm; LCSC C8353
TB3: PUMP_MOTOR; TerminalBlock_KF301-2P_P5.00mm; LCSC C8352
TB4: EXT_POWER_BAT; TerminalBlock_KF301-3P_P5.00mm_Vertical; LCSC C8353
U1: ESP32-C3-WROOM-02; LCSC C2934560
U2: AMS1117-3.3; SOT-223-3_TabPin2; LCSC C6186

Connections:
+3V3: C8.1, C11.1, C12.1, D3.1 (A), D4.1 (A), MOD1.1, MOD2.1, R10.1, R11.1, R_LDR1.1, U1.1 (3V3), U2.2 (VO)
+5V: C7.1, C10.1, D1.1 (K), D2.1 (K), J1.A4 (VBUS), J1.A9 (VBUS), J1.B4 (VBUS), J1.B9 (VBUS), R1.1, TB1.1, TB3.1, U2.3 (VI)
ECHO_5V: R3.1, TB1.3
ESP_EN: C9.2, R10.2, SW1.1, U1.2 (EN)
EXT_5V: D2.2 (A), TB4.1
GATE_DRIVE: Q1.1 (G), R5.2, R6.1
GND: C1.1, C2.2, C4.1, C6.2, C7.2, C8.2, C9.1, C10.2, C11.2, C12.2, H1.1, H2.1, H3.1, H4.1, J1.A1 (GND), J1.A12 (GND), J1.B1 (GND), J1.B12 (GND), J1.SH (SHIELD), MOD1.2, MOD2.2, MOD2.5, Q1.2 (S), R2.1, R4.2, R6.2, R7.1, R9.2, R12.2, R13.2, R14.2, SW1.2, SW2.1, TB1.4, TB2.3, TB4.2, U1.9 (GND), U1.19 (GND), U2.1 (GND)
GPIO0_5V_ADC: C1.2, R1.2, R2.2, U1.18 (IO0)
GPIO1_SOIL: C2.1, TB2.1, U1.17 (IO1)
GPIO3_LDR: C4.2, R7.2, R_LDR1.2, U1.15 (IO3)
GPIO4_VBAT_ADC: C6.1, R8.1, R9.1, U1.3 (IO4)
GPIO5_SOIL_VCC: TB2.2, U1.4 (IO5)
GPIO6_ECHO: R3.2, R4.1, U1.5 (IO6)
GPIO7_GATE: R5.1, U1.6 (IO7)
GPIO8_LED: R15.2, U1.7 (IO8)
GPIO9_BOOT: R11.2, SW2.2, U1.8 (IO9)
GPIO10_TRIG: TB1.2, U1.10 (IO10)
GPIO20_SDA: MOD1.4, MOD2.4, U1.11 (IO20/RXD)
GPIO21_SCL: MOD1.3, MOD2.3, U1.12 (IO21/TXD)
PUMP_DRAIN: D1.2 (A), Q1.3 (D), TB3.2
PWR_LED_K: D3.2 (K), R14.1
STAT_LED_K: D4.2 (K), R15.1
USB_CC1: J1.A5 (CC1), R12.1
USB_CC2: J1.B5 (CC2), R13.1
USB_DN: J1.A7 (D-), J1.B7 (D-), U1.13 (IO18)
USB_DP: J1.A6 (D+), J1.B6 (D+), U1.14 (IO19)
VBAT_SENSE: R8.2, TB4.3

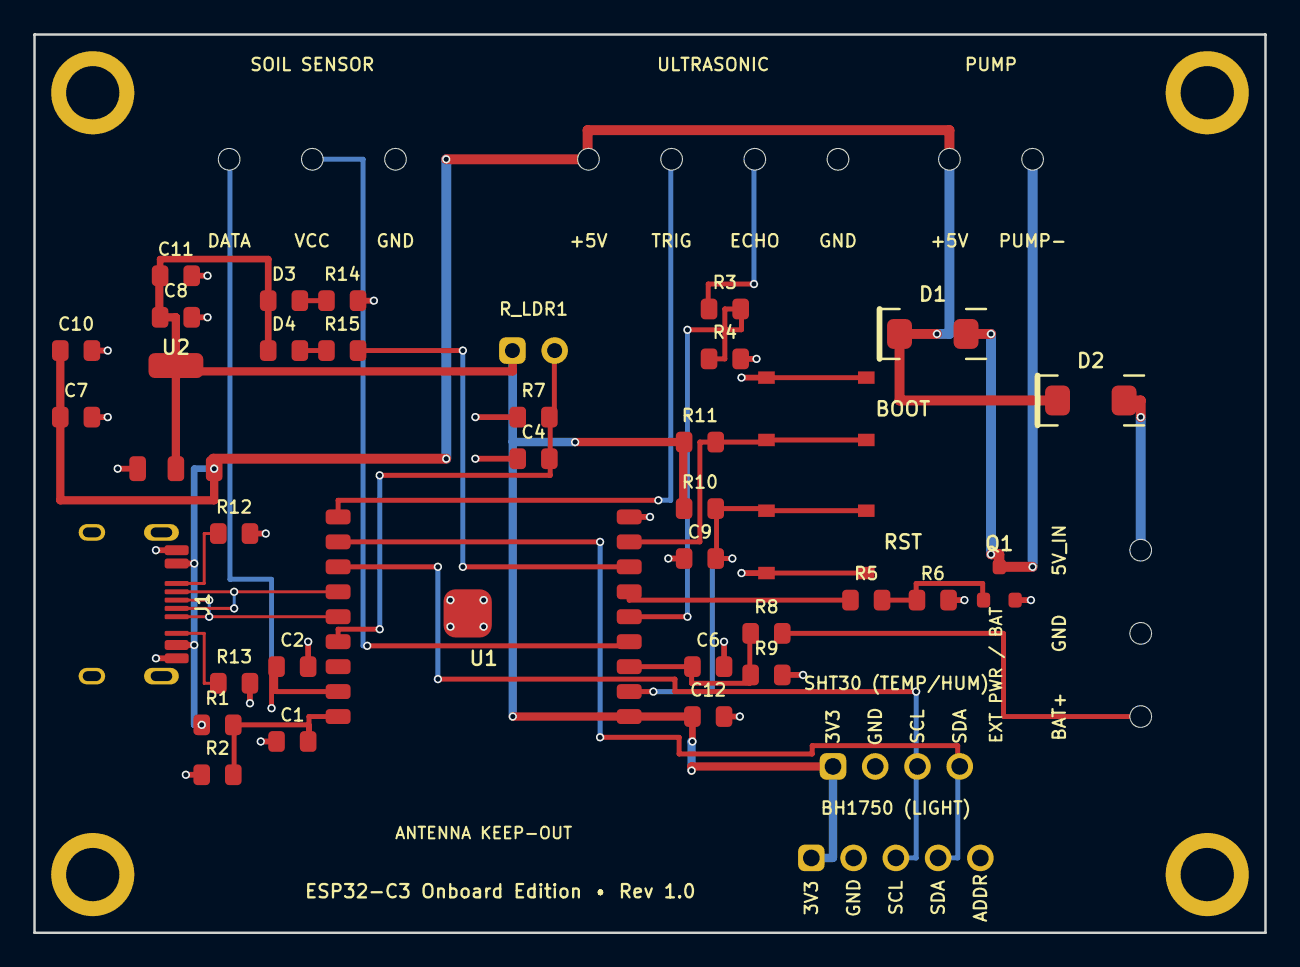
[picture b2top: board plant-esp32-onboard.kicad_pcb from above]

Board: 2 copper layers, 74.0 x 54.0 mm, 46 parts (0 on the bottom side), 27 nets.

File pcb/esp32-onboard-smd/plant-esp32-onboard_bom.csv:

Comment,Designator,Footprint,LCSC Part #
"100k","R1,R2,R8,R9,R6","0805","C149504"
"100nF","C7,C8,C1,C6,C2,C4","0805","C28233"
"10k","R11,R10,R7","0805","C17414"
"10uF","C10,C11","0805","C15850"
"1k","R14,R15,R3,R5","0805","C17513"
"1uF","C9","0805","C28323"
"22uF","C12","0805","C45783"
"2k","R4","0805","C17604"
"5.1k","R12,R13","0805","C27834"
"AMS1117-3.3","U2","SOT-223","C6186"
"AO3400A","Q1","SOT-23","C20917"
"ESP32-C3-WROOM-02","U1","ESP32-C3-WROOM-02","C2934560"
"PWR_GREEN","D3","0805","C2297"
"SS34","D1,D2","SMA_DO-214AC","C8678"
"STAT_BLUE","D4","0805","C2293"
"TS-1187A","SW1,SW2","TS-1187A","C318884"
"TYPE-C-16P","J1","TYPE-C-16P","C165948"

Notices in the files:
README.md:
License: GPL v3
License: CERN-OHL-S v2
